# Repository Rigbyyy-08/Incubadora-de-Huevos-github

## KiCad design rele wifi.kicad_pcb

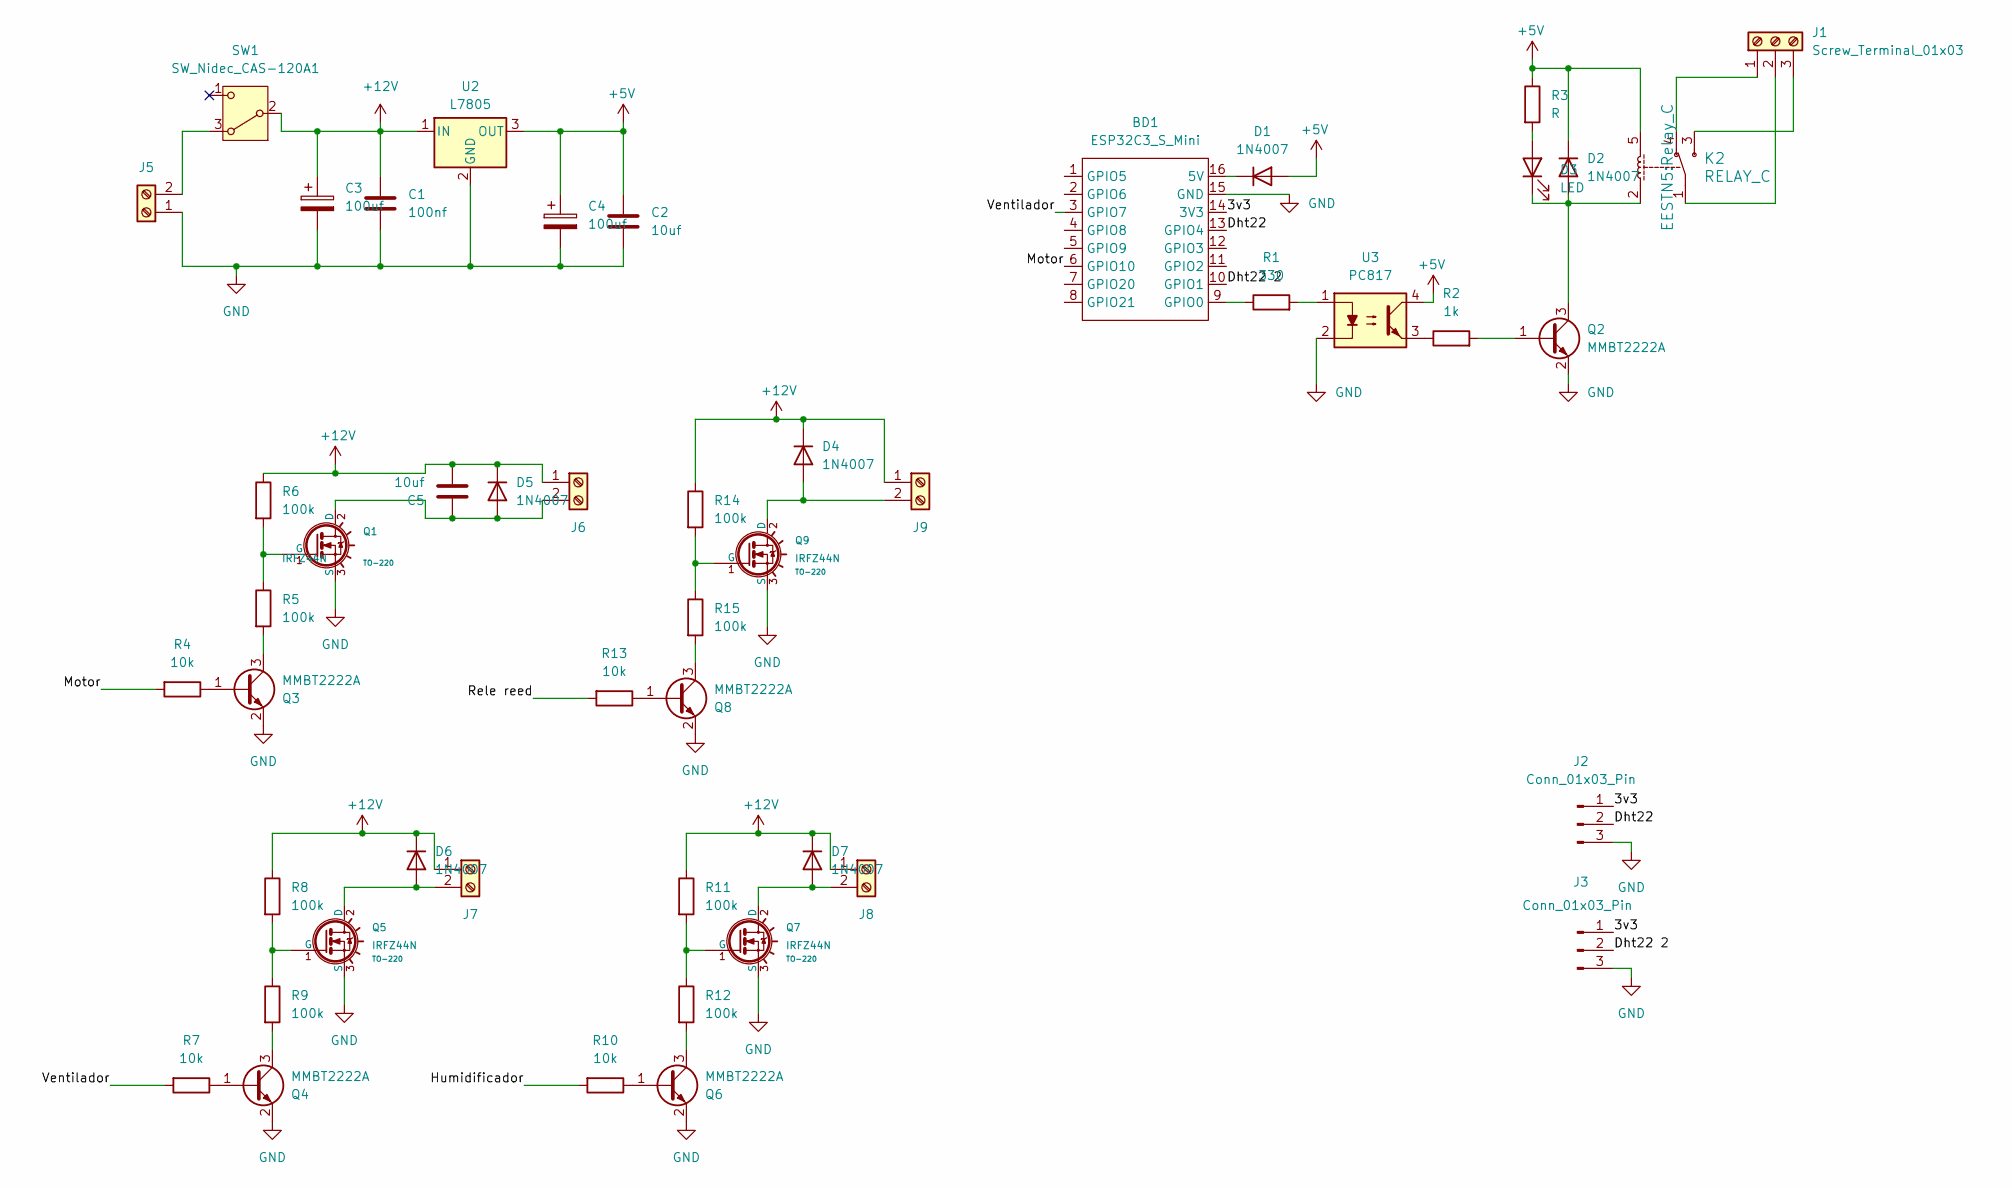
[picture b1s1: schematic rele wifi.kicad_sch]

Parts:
BD1: ESP32C3_S_Mini; ESP32_C3_SM
C1: 100nf; C_0805_2012Metric
C2, C5: 10uf; C_0805_2012Metric
C3, C4: 100uf; CP_Elec_6.3x7.7
D1, D2, D4, D5, D6, D7: 1N4007; D_SMA
D3: LED; LED_0805_2012Metric
J1: Screw_Terminal_01x03; TerminalBlock_MaiXu_MX126-5.0-03P_1x03_P5.00mm
J2, J3: Conn_01x03_Pin; Pin_Strip_3
J5, J6, J7, J8, J9: Screw_Terminal_01x02; TerminalBlock_MaiXu_MX126-5.0-02P_1x02_P5.00mm
K2: RELAY_C; Relay_C
Q1, Q5, Q7, Q9: IRFZ44N; TO-220
Q2, Q3, Q4, Q6, Q8: MMBT2222A; SOT-23
R1: 330; R_0805_2012Metric
R2: 1k; R_Axial_DIN0204_L3.6mm_D1.6mm_P5.08mm_Horizontal
R3: R; R_0805_2012Metric
R4, R7, R10, R13: 10k; R_0805_2012Metric
R5, R6, R8, R9, R11, R12, R14, R15: 100k; R_Axial_DIN0207_L6.3mm_D2.5mm_P10.16mm_Horizontal
SW1: SW_Nidec_CAS-120A1; SW_SPDT_TH_Vertical
U2: L7805; TO-263-3_TabPin2
U3: PC817; SOP-4_7.5x4.1mm_P2.54mm

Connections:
+5V: C2.1, C4.1, D1.2 (A), D2.1 (K), K2.5, R3.1, U2.3 (OUT), U3.4
+12V: C1.1, C3.1, C5.2, D4.1 (K), D5.1 (K), D6.1 (K), D7.1 (K), J6.1, J7.1, J8.1, J9.1, R6.1, R8.1, R11.1, R14.1, SW1.2 (B), U2.1 (IN)
/3v3: BD1.14 (3V3), J2.1, J3.1
/Dht22: BD1.13 (GPIO4), J2.2
/Dht22 2: BD1.10 (GPIO1), J3.2
/Motor: BD1.6 (GPIO10), R4.2
/Rele reed: BD1.4 (GPIO8), R13.2
GND: BD1.15 (GND), C1.2, C2.2, C3.2, C4.2, J2.3, J3.3, J5.1, Q1.3 (S), Q2.2 (E), Q3.2 (E), Q4.2 (E), Q5.3 (S), Q6.2 (E), Q7.3 (S), Q8.2 (E), Q9.3 (S), U2.2 (GND), U3.2
unnamed: BD1.16 (5V), D1.1 (K)
unnamed: BD1.9 (GPIO0), R1.1
unnamed: D2.2 (A), D3.1 (K), K2.2, Q2.3 (C)
unnamed: D3.2 (A), R3.2
unnamed: D4.2 (A), J9.2, Q9.2 (D)
unnamed: C5.1, D5.2 (A), J6.2, Q1.2 (D)
unnamed: D6.2 (A), J7.2, Q5.2 (D)
unnamed: D7.2 (A), J8.2, Q7.2 (D)
unnamed: J1.1, K2.4
unnamed: J1.2, K2.1
unnamed: J1.3, K2.3
unnamed: J5.2, SW1.3 (A)
unnamed: Q1.1 (G), R5.1, R6.2
unnamed: Q2.1 (B), R2.2
unnamed: Q3.1 (B), R4.1
unnamed: Q3.3 (C), R5.2
unnamed: Q4.1 (B), R7.1
unnamed: Q4.3 (C), R9.2
unnamed: Q5.1 (G), R8.2, R9.1
unnamed: Q6.1 (B), R10.1
unnamed: Q6.3 (C), R12.2
unnamed: Q7.1 (G), R11.2, R12.1
unnamed: Q8.1 (B), R13.1
unnamed: Q8.3 (C), R15.2
unnamed: Q9.1 (G), R14.2, R15.1
unnamed: R1.2, U3.1
unnamed: R2.1, U3.3

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
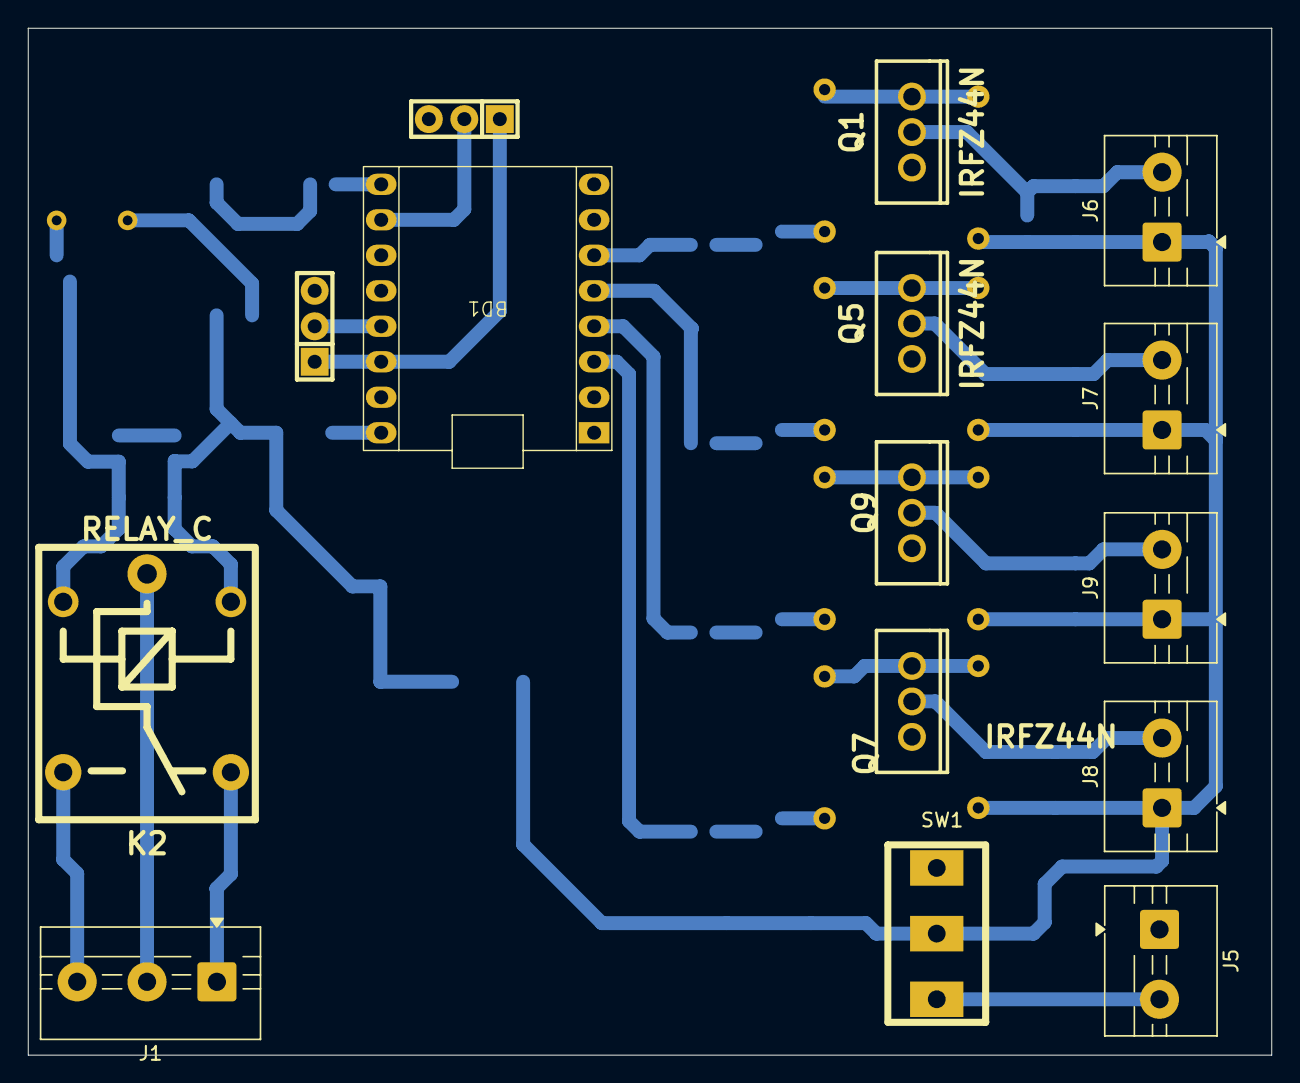
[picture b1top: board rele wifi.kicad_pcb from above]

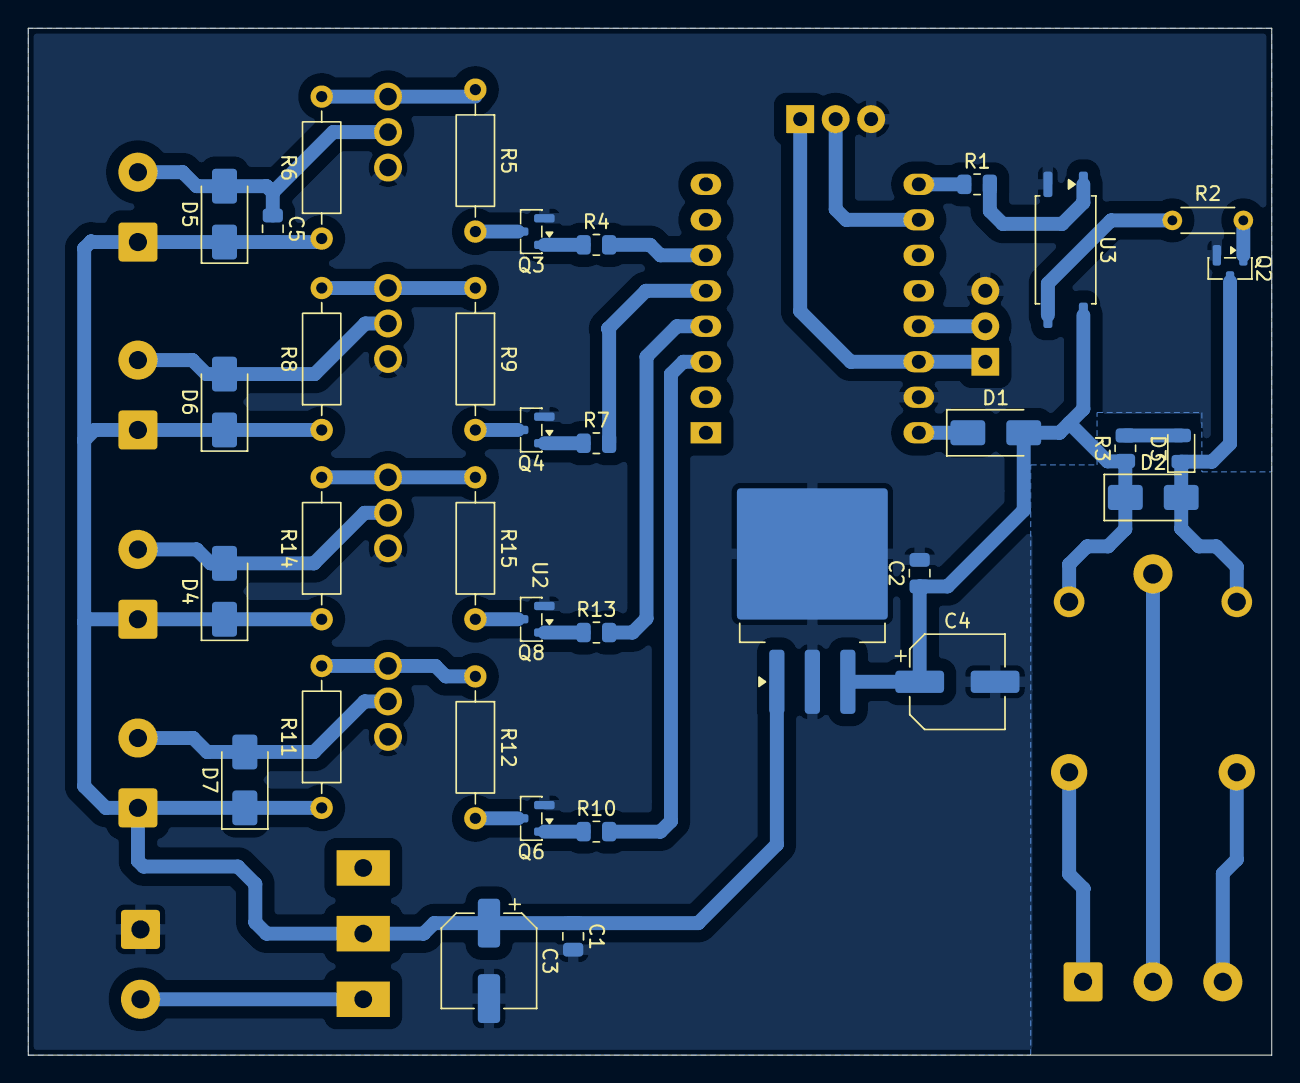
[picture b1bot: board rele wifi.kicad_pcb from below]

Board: 2 copper layers, 89.0 x 73.5 mm, 49 parts (34 on the bottom side), 37 nets.
